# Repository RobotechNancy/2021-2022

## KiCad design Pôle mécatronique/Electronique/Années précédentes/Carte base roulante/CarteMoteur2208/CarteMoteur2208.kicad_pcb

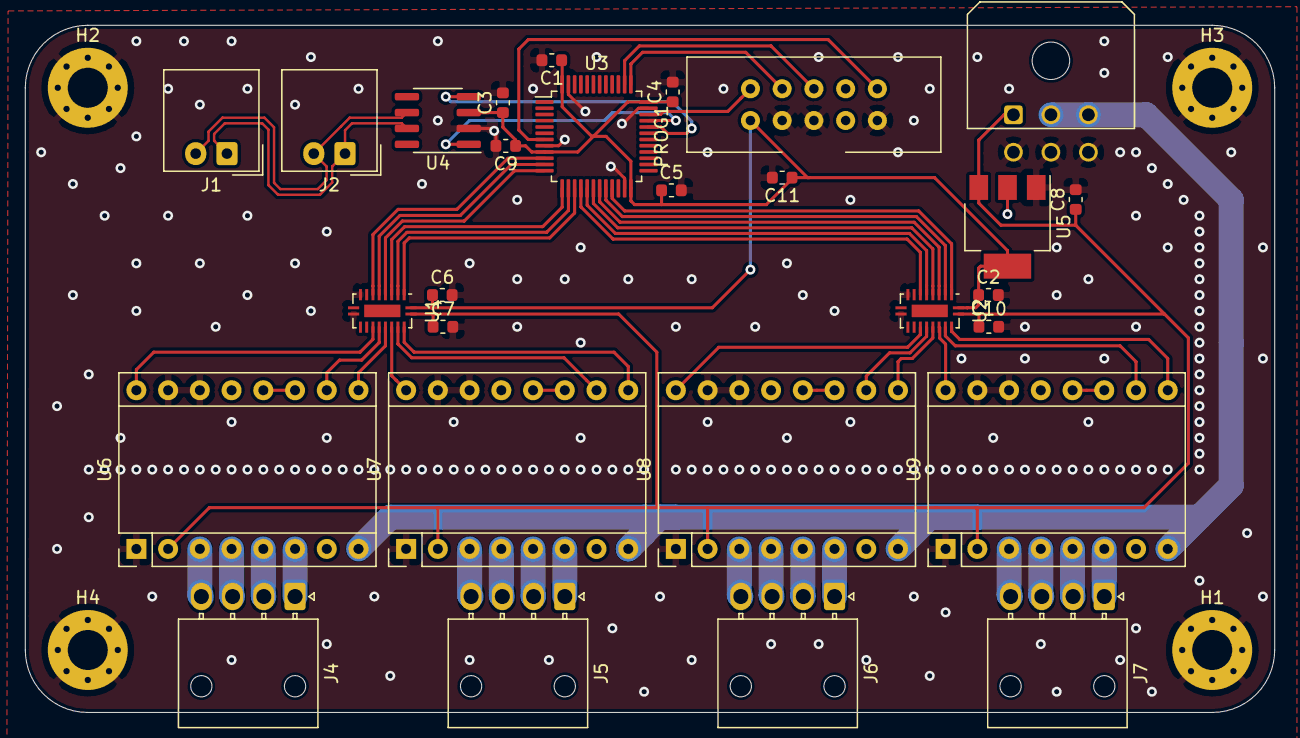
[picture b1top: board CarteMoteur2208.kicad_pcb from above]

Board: 2 copper layers, 100.0 x 55.0 mm, 32 parts (0 on the bottom side), 56 nets.

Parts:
C1, C2, C3, C4, C5, C6, C7, C8, C9, C10: 104; C_0603_1608Metric
C11: 106; C_0603_1608Metric
H1, H2, H3, H4: MountingHole_Pad; MountingHole_3.2mm_M3_Pad_Via
J1, J2: Conn_01x02; Molex_SPOX_5268-02A_1x02_P2.50mm_Horizontal
J3: Conn_02x03_Counter_Clockwise; Molex_Micro-Fit_3.0_43045-0600_2x03_P3.00mm_Horizontal
J4, J5, J6, J7: Conn_01x04; Molex_Nano-Fit_105313-xx04_1x04_P2.50mm_Horizontal
PROG1: STM32_SW; JTAG10
U1, U2: FXMA108; WQFN-20-1EP_2.5x4.5mm_P0.5mm_EP1x2.9mm
U3: STM32F103C8Tx; LQFP-48_7x7mm_P0.5mm
U4: TCAN337; SOIC-8_3.9x4.9mm_P1.27mm
U5: LT1117-3.3; SOT-223-3_TabPin2
U6, U7, U8, U9: TMC2208; Pololu_Breakout-16_15.2x20.3mm

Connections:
+3V3: C1.1, C2.1, C3.1, C4.1, C5.1, C6.1, C9.1, C11.1, PROG1.1, U1.1, U2.1, U3.9, U3.24, U3.36, U3.48, U4.3, U5.2
+5V: C7.1, C8.1, C10.1, J3.1, U1.20, U2.20, U5.3, U6.2, U7.2, U8.2, U9.2
+BATT: J3.2, J3.3, U6.8, U7.8, U8.8, U9.8
/CAN_N: J1.2, J2.2, U4.6
/CAN_P: J1.1, J2.1, U4.7
/CAN_RX: U3.32, U4.4
/CAN_TX: U3.33, U4.1
/DIR1_H: U1.16, U6.9
/DIR1_L: U1.5, U3.12
/DIR2_H: U1.19, U7.9
/DIR2_L: U1.2, U3.15
/DIR3_H: U2.16, U8.9
/DIR3_L: U2.5, U3.18
/DIR4_H: U2.19, U9.9
/DIR4_L: U2.2, U3.21
/EN1_H: U1.14, U6.16
/EN1_L: U1.7, U3.10
/EN2_H: U1.17, U7.16
/EN2_L: U1.4, U3.13
/EN3_H: U2.14, U8.16
/EN3_L: U2.7, U3.16
/EN4_H: U2.17, U9.16
/EN4_L: U2.4, U3.19
/NRST: PROG1.10, U3.7
/STEP1_H: U1.15, U6.10
/STEP1_L: U1.6, U3.11
/STEP2_H: U1.18, U7.10
/STEP2_L: U1.3, U3.14
/STEP3_H: U2.15, U8.10
/STEP3_L: U2.6, U3.17
/STEP4_H: U2.18, U9.10
/STEP4_L: U2.3, U3.20
/SWCLK: PROG1.4, U3.37
/SWDIO: PROG1.2, U3.34
/SWO: PROG1.6, U3.38
GND: C1.2, C2.2, C3.2, C4.2, C5.2, C6.2, C7.2, C8.2, C9.2, C10.2, C11.2, H1.1, H2.1, H3.1, H4.1, J3.4, J3.5, J3.6, PROG1.3, PROG1.5, PROG1.9, U1.8, U1.9, U1.10, U1.11, U2.8, U2.9, U2.10, U2.11, U3.8, U3.23, U3.35, U3.47, U4.2, U5.1, U6.1, U6.14, U6.15, U7.1, U7.14, U7.15, U8.1, U8.14, U8.15, U9.1, U9.14, U9.15
unnamed: J4.1, U6.6
unnamed: J4.2, U6.5
unnamed: J4.3, U6.4
unnamed: J4.4, U6.3
unnamed: J5.1, U7.6
unnamed: J5.2, U7.5
unnamed: J5.3, U7.4
unnamed: J5.4, U7.3
unnamed: J6.1, U8.6
unnamed: J6.2, U8.5
unnamed: J6.3, U8.4
unnamed: J6.4, U8.3
unnamed: J7.1, U9.6
unnamed: J7.2, U9.5
unnamed: J7.3, U9.4
unnamed: J7.4, U9.3
unnamed: U6.11, U6.12
unnamed: U7.11, U7.12
unnamed: U8.11, U8.12
unnamed: U9.11, U9.12

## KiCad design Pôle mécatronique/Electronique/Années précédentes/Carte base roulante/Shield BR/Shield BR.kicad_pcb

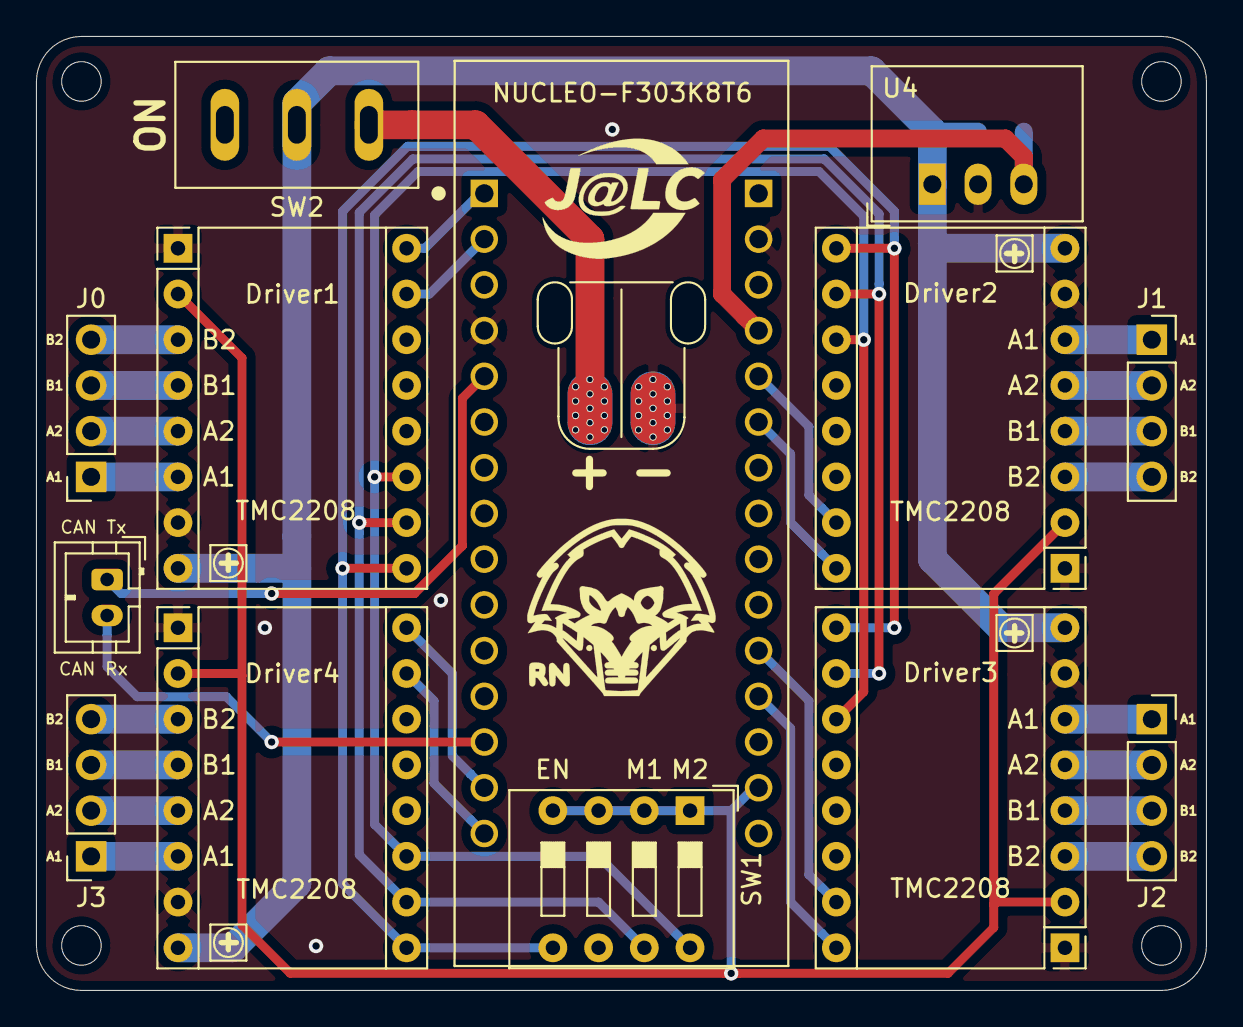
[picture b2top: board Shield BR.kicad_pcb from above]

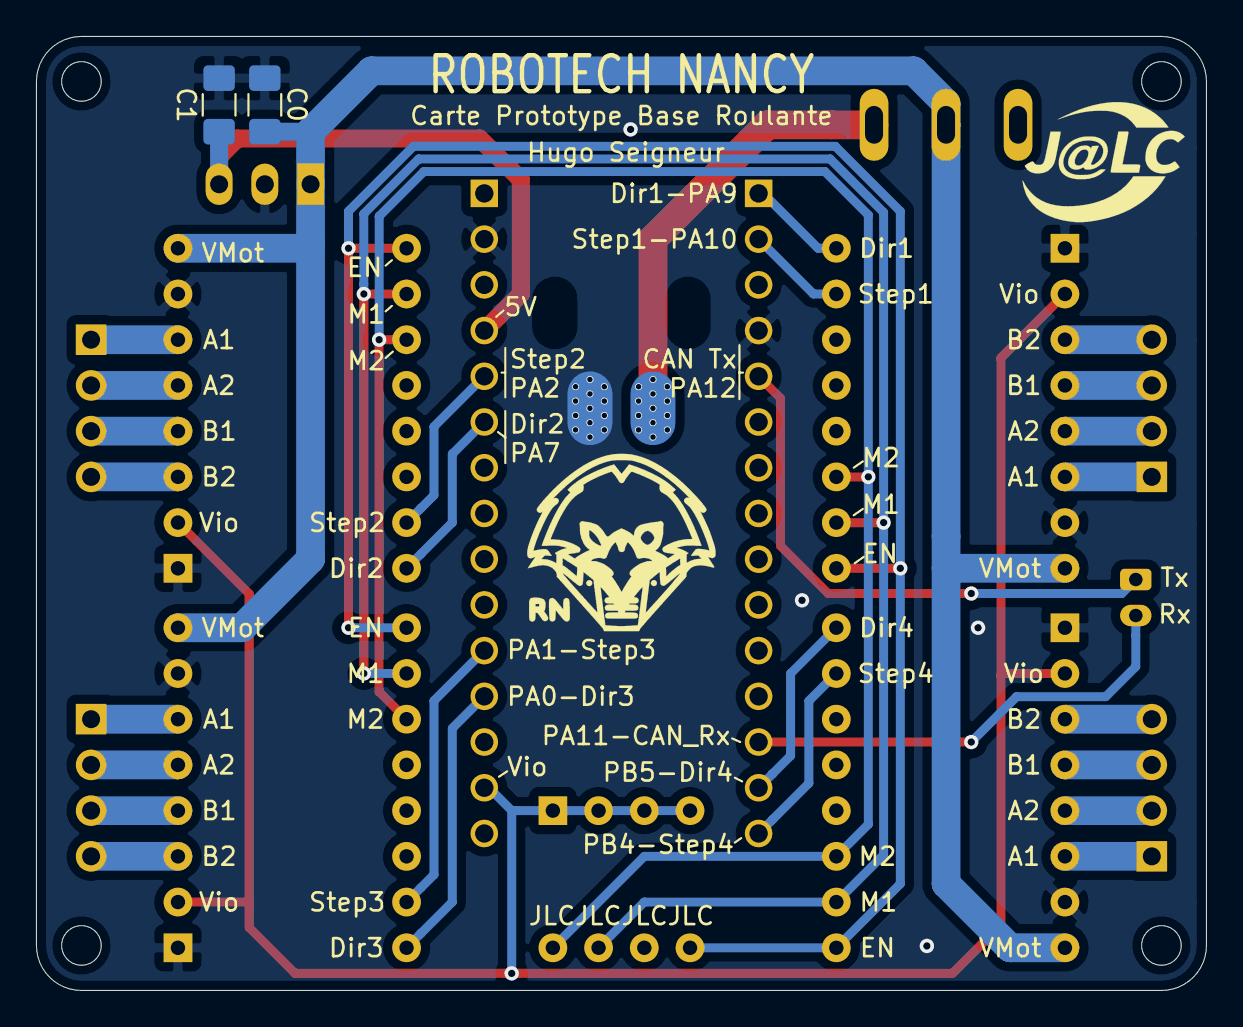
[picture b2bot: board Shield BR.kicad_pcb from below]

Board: 2 copper layers, 65.0 x 53.0 mm, 20 parts (2 on the bottom side), 34 nets.

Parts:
C0, C1: 10u; C_1206_3216Metric_Pad1.42x1.75mm_HandSolder
Driver1, Driver2, Driver3, Driver4: TMC2208; TMC_2208_BOB
H0, H1, H2, H3: MountingHole; MountingHole_2.2mm_M2_ISO7380
J0, J1, J2, J3: Conn_01x04_Female; PinSocket_1x04_P2.54mm_Vertical
J4: Conn_01x04_Male; Alim_Cablée_2_fils
J5: Conn_01x02_Female; JST_PH_B2B-PH-K_1x02_P2.00mm_Vertical
NUCLEO-F303K8T6: NUCLEO-F303K8; MODULE_NUCLEO-F303K8
SW1: SW_DIP_x04; SW_DIP_SPSTx04_Slide_9.78x12.34mm_W7.62mm_P2.54mm
SW2: SW_Push_SPDT; Switch_3_Pin
U4: R-78E5.0-0.5; Converter_DCDC_RECOM_R-78E-0.5_THT

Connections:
+5V: C1.1, NUCLEO-F303K8T6.4.4, U4.3
+BATT: C0.1, Driver1.8, Driver2.8, Driver3.8, Driver4.8, SW2.2, U4.1
CAN_Rx: J5.2, NUCLEO-F303K8T6.3.13
CAN_Tx: J5.1, NUCLEO-F303K8T6.3.5
Dir0: Driver1.9, NUCLEO-F303K8T6.3.1
Dir1: Driver2.9, NUCLEO-F303K8T6.4.6
Dir2: Driver3.9, NUCLEO-F303K8T6.4.12
Dir3: Driver4.9, NUCLEO-F303K8T6.3.14
EN: Driver1.16, Driver2.16, Driver3.16, Driver4.16, SW1.5
GND: C0.2, C1.2, Driver1.1, Driver1.7, Driver2.1, Driver2.7, Driver3.1, Driver3.7, Driver4.1, Driver4.7, J4.2, NUCLEO-F303K8T6.3.4, NUCLEO-F303K8T6.4.2, U4.2
M1: Driver1.15, Driver2.15, Driver3.15, Driver4.15, SW1.7
M2: Driver1.14, Driver2.14, Driver3.14, Driver4.14, SW1.8
unnamed: Driver1.3, J0.4
unnamed: Driver1.4, J0.3
unnamed: Driver1.5, J0.2
unnamed: Driver1.6, J0.1
unnamed: Driver2.3, J1.4
unnamed: Driver2.4, J1.3
unnamed: Driver2.5, J1.2
unnamed: Driver2.6, J1.1
unnamed: Driver3.3, J2.4
unnamed: Driver3.4, J2.3
unnamed: Driver3.5, J2.2
unnamed: Driver3.6, J2.1
unnamed: Driver4.3, J3.4
unnamed: Driver4.4, J3.3
unnamed: Driver4.5, J3.2
unnamed: Driver4.6, J3.1
unnamed: J4.1, SW2.1
Stp0: Driver1.10, NUCLEO-F303K8T6.3.2
Stp1: Driver2.10, NUCLEO-F303K8T6.4.5
Stp2: Driver3.10, NUCLEO-F303K8T6.4.11
Stp3: Driver4.10, NUCLEO-F303K8T6.3.15
Vio: Driver1.2, Driver2.2, Driver3.2, Driver4.2, NUCLEO-F303K8T6.4.14, SW1.1, SW1.2, SW1.3, SW1.4

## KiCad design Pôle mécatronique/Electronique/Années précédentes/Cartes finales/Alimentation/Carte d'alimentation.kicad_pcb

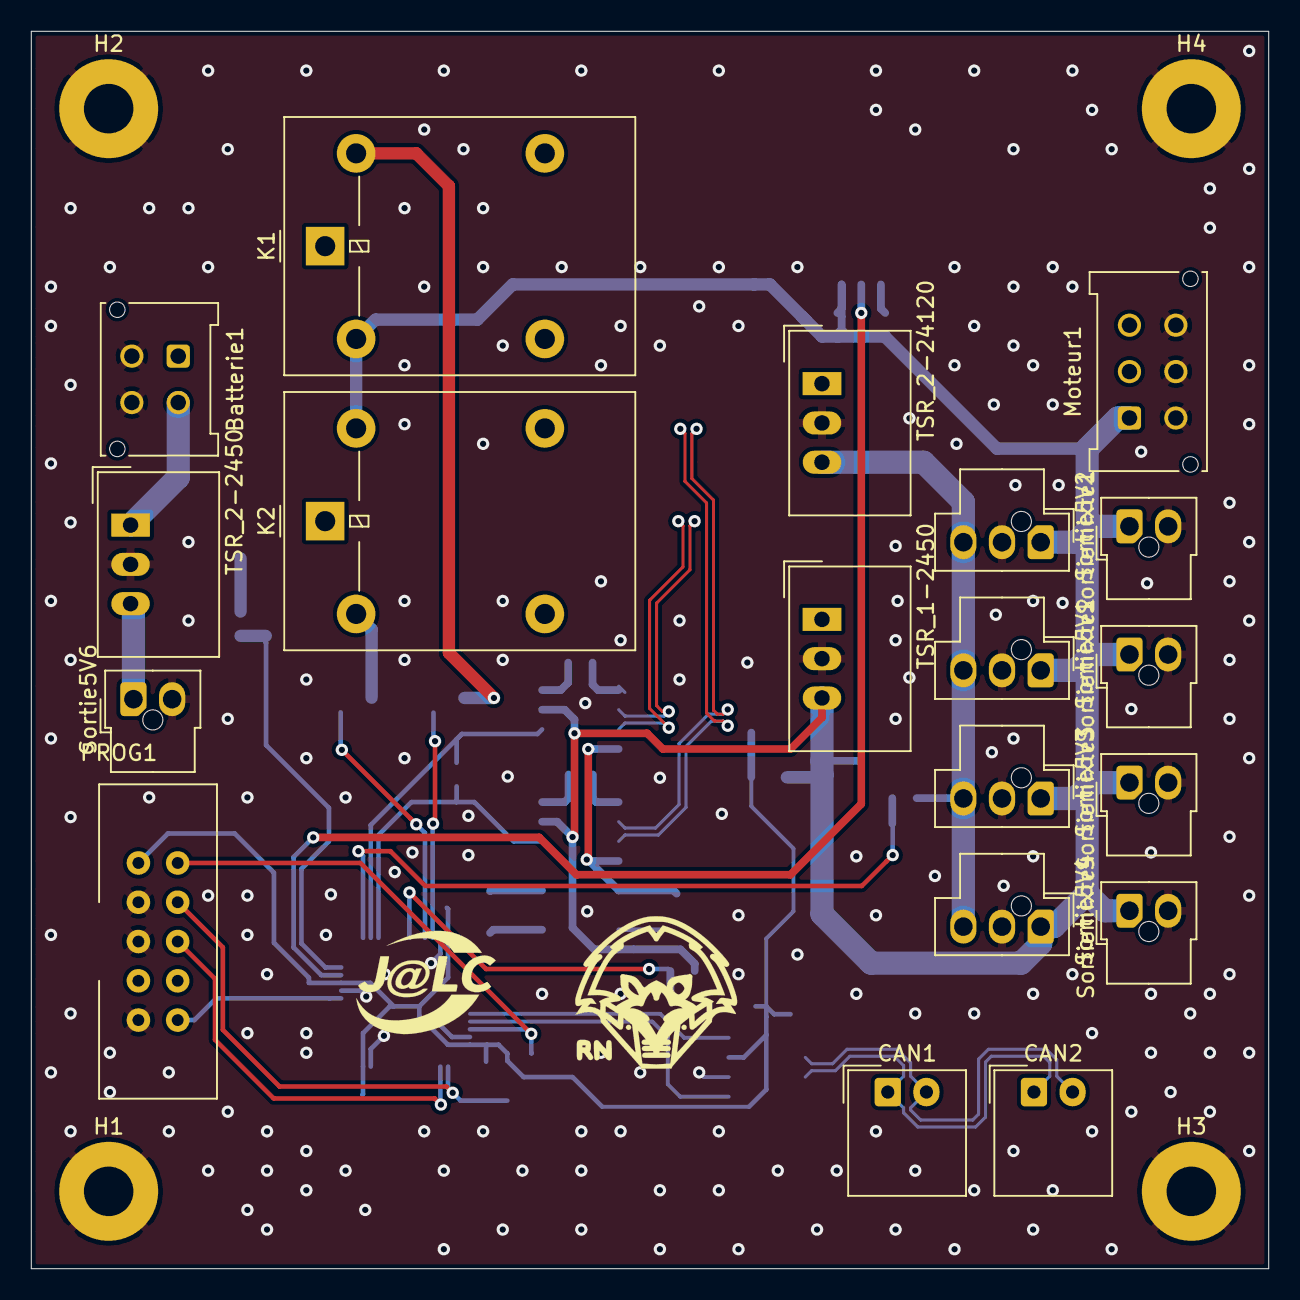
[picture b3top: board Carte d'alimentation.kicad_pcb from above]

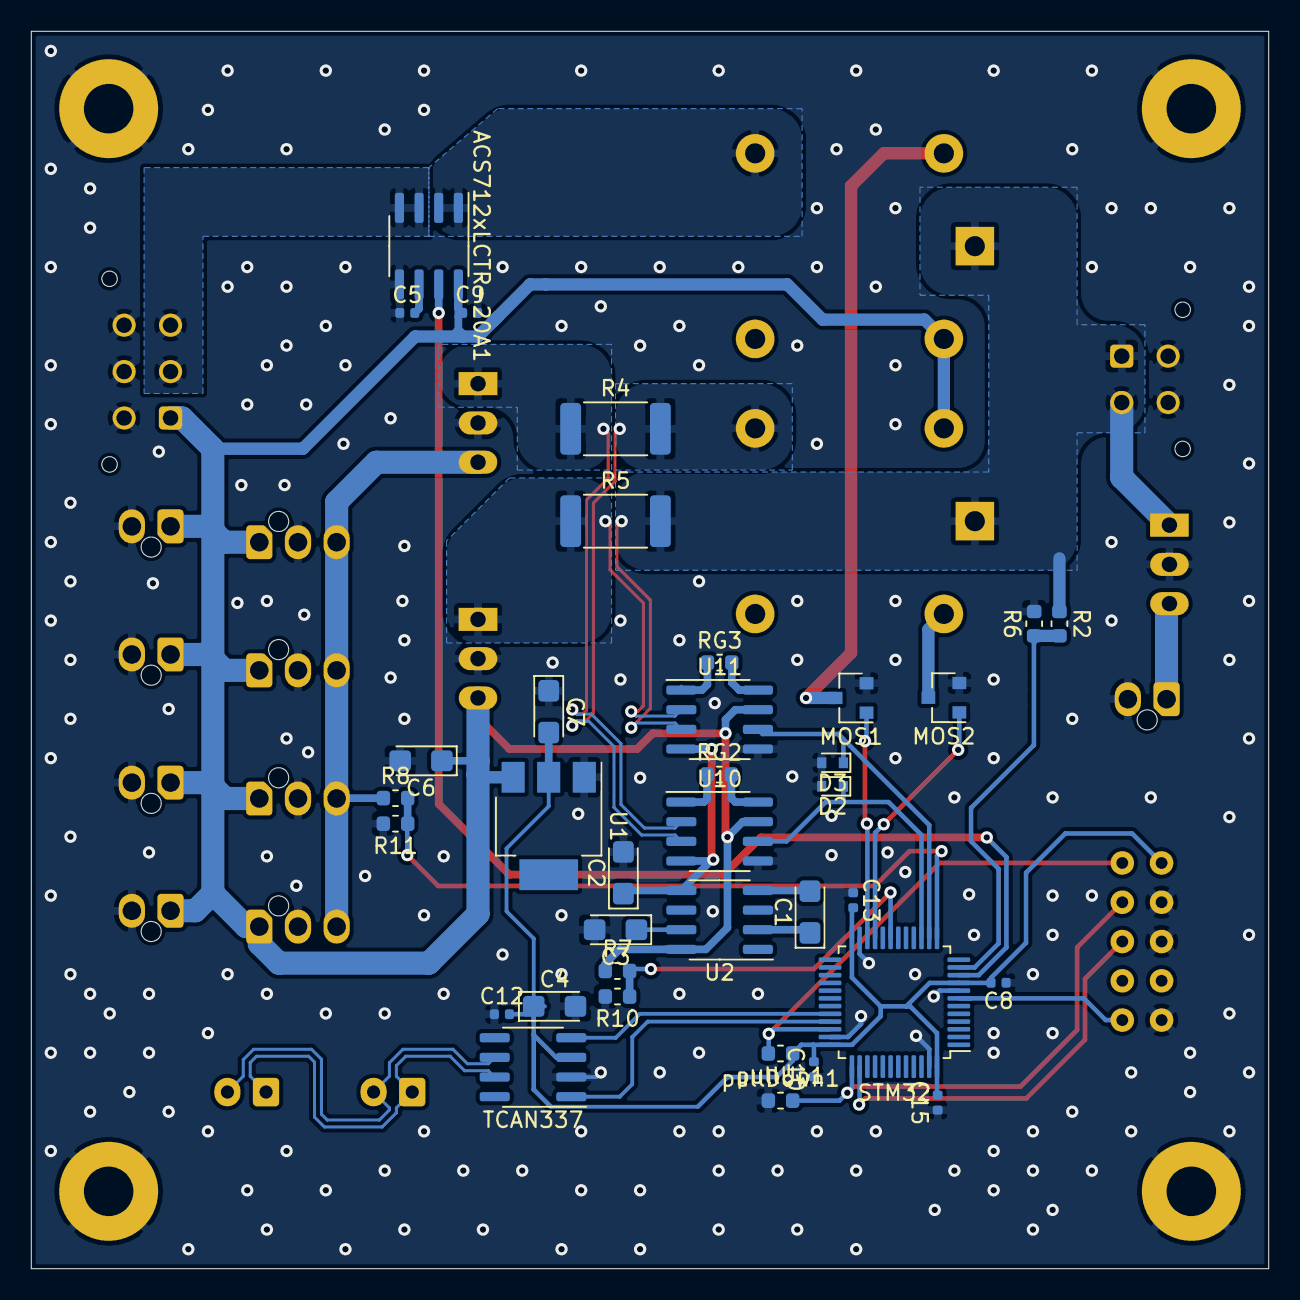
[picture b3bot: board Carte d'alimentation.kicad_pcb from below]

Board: 2 copper layers, 80.0 x 80.0 mm, 59 parts (36 on the bottom side), 38 nets.

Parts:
ACS712xLCTR-20A1: ACS712xLCTR-20A; SOIC-8_3.9x4.9mm_P1.27mm
Batterie1: Batterie; Molex_Micro-Fit_3.0_43045-0412_2x02_P3.00mm_Vertical
C1, C2, C3, C6, C7: 10µF; CP_EIA-3216-10_Kemet-I
C4: 1µF; CP_EIA-3216-10_Kemet-I
C5, C8, C9, C10, C12, C13, C15: 1nF; C_0402_1005Metric
CAN1, CAN2: sortie CAN; Molex_SPOX_5268-02A_1x02_P2.50mm_Horizontal
D2, D3: D_Zener; D_SOD-523
H1, H2, H3, H4: MountingHole_Pad; MountingHole_3.2mm_M3_Pad
K1, K2: G5LE-1; Relay_SPDT_Omron-G5LE-1
MOS1, MOS2: 2N7002; SOT-23
Moteur1: Moteur; Molex_Micro-Fit_3.0_43045-0612_2x03_P3.00mm_Vertical
PROG1: STM32_SW; JTAG10
R2: 90k; R_0603_1608Metric
R4, R5: 0.035; R_2512_6332Metric
R6, R7: 10k; R_0603_1608Metric
R8: 56k; R_0603_1608Metric
R10, R11: 20k; R_0603_1608Metric
RG2: 1150; R_0603_1608Metric
RG3: 560; R_0603_1608Metric
STM32: STM32F103C8Tx; LQFP-48_7x7mm_P0.5mm
Sortie5V1, Sortie5V2, Sortie5V3, Sortie5V4, Sortie5V6: Sortie 5V; Molex_Nano-Fit_105309-xx02_1x02_P2.50mm_Vertical
Sortiemixte1, Sortiemixte2, Sortiemixte3, Sortiemixte4: Sortie mixte; Molex_Nano-Fit_105309-xx03_1x03_P2.50mm_Vertical
TCAN337: TCAN337; SOIC-8_3.9x4.9mm_P1.27mm
TSR_1-2450: TSR_1-2450; Converter_DCDC_TRACO_TSR-1_THT
TSR_2-2450: TSR_2-2450; Converter_DCDC_TRACO_TSR-1_THT
TSR_2-24120: TSR_2-24120; Converter_DCDC_TRACO_TSR-1_THT
U1: LM1117-3.3; SOT-223
U2: ICL7660; SOIC-8_3.9x4.9mm_P1.27mm
U10, U11: AD620; SOIC-8_3.9x4.9mm_P1.27mm
pullDown1: 1k; R_0603_1608Metric
pullUp1: 1k; R_0603_1608Metric

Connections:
3.3V: C4.1, C7.2, C8.2, C10.2, C12.2, C13.2, C15.2, PROG1.1, STM32.9, STM32.24, STM32.36, STM32.48, TCAN337.3, U1.2, pullUp1.1
5VDCRasPi: Sortie5V6.1, TSR_2-2450.3
+5V: ACS712xLCTR-20A1.8, C6.1, C9.1, K1.2, K2.5, Moteur1.1, R7.1, Sortie5V1.1, Sortie5V2.1, Sortie5V3.1, Sortie5V4.1, Sortiemixte1.1, Sortiemixte2.1, Sortiemixte3.1, Sortiemixte4.1, TSR_1-2450.3, U1.3, U2.8, U10.7, U11.7
+12V: R8.1, Sortiemixte1.3, Sortiemixte2.3, Sortiemixte3.3, Sortiemixte4.3, TSR_2-24120.3
-5V: C2.1, U2.5, U10.4, U11.4
/AD5_N: R5.1, TSR_1-2450.1, U11.2
/AD12_N: R4.1, TSR_2-24120.1, U10.2
/AD12_P: K2.4, R4.2, U10.3
GND: ACS712xLCTR-20A1.5, Batterie1.3, Batterie1.4, C2.2, C3.2, C4.2, C5.1, C6.2, C7.1, C8.1, C9.2, C10.1, C12.1, C13.1, C15.1, D2.2, D3.2, H1.1, H2.1, H3.1, H4.1, MOS1.2, MOS2.2, Moteur1.4, Moteur1.5, Moteur1.6, PROG1.3, PROG1.5, PROG1.9, R6.2, R10.2, R11.2, STM32.8, STM32.23, STM32.35, STM32.47, Sortie5V1.2, Sortie5V2.2, Sortie5V3.2, Sortie5V4.2, Sortie5V6.2, Sortiemixte1.2, Sortiemixte2.2, Sortiemixte3.2, Sortiemixte4.2, TCAN337.2, TSR_1-2450.2, TSR_2-2450.2, TSR_2-24120.2, U1.1, U2.3, U10.5, U11.5, pullDown1.1
I_5VDC: D3.1, STM32.14, U11.6
I_12VDC: D2.1, STM32.15, U10.6
I_VBatt: ACS712xLCTR-20A1.7, STM32.10
Mes_5VDC: R7.2, R10.1, STM32.19
Mes_12VDC: R8.2, R11.1, STM32.13
Mes_VBatt: R2.2, R6.1, STM32.11
NRST: PROG1.10, STM32.7
unnamed: ACS712xLCTR-20A1.1, ACS712xLCTR-20A1.2, K1.4
unnamed: ACS712xLCTR-20A1.6, C5.2
unnamed: C1.1, U2.2
unnamed: C1.2, U2.4
unnamed: C3.1, U2.7
unnamed: K1.5, MOS1.3
unnamed: K2.2, MOS2.3
unnamed: RG2.1, U10.1
unnamed: RG2.2, U10.8
unnamed: RG3.1, U11.1
unnamed: RG3.2, U11.8
Out_VBatt: ACS712xLCTR-20A1.3, ACS712xLCTR-20A1.4, Moteur1.2, Moteur1.3
Relay_12V: MOS2.1, STM32.21
Relay_VBatt: MOS1.1, STM32.22
Rx: STM32.32, TCAN337.4
SWCLK: PROG1.4, STM32.37, pullDown1.2
SWDIO: PROG1.2, STM32.34, pullUp1.2
SWO: PROG1.6, STM32.38
Tx: STM32.33, TCAN337.1
VBatt: Batterie1.1, Batterie1.2, K1.1, K2.1, R2.1, R5.2, TSR_2-2450.1, U11.3
can_N: CAN1.2, CAN2.2, TCAN337.6
can_P: CAN1.1, CAN2.1, TCAN337.7

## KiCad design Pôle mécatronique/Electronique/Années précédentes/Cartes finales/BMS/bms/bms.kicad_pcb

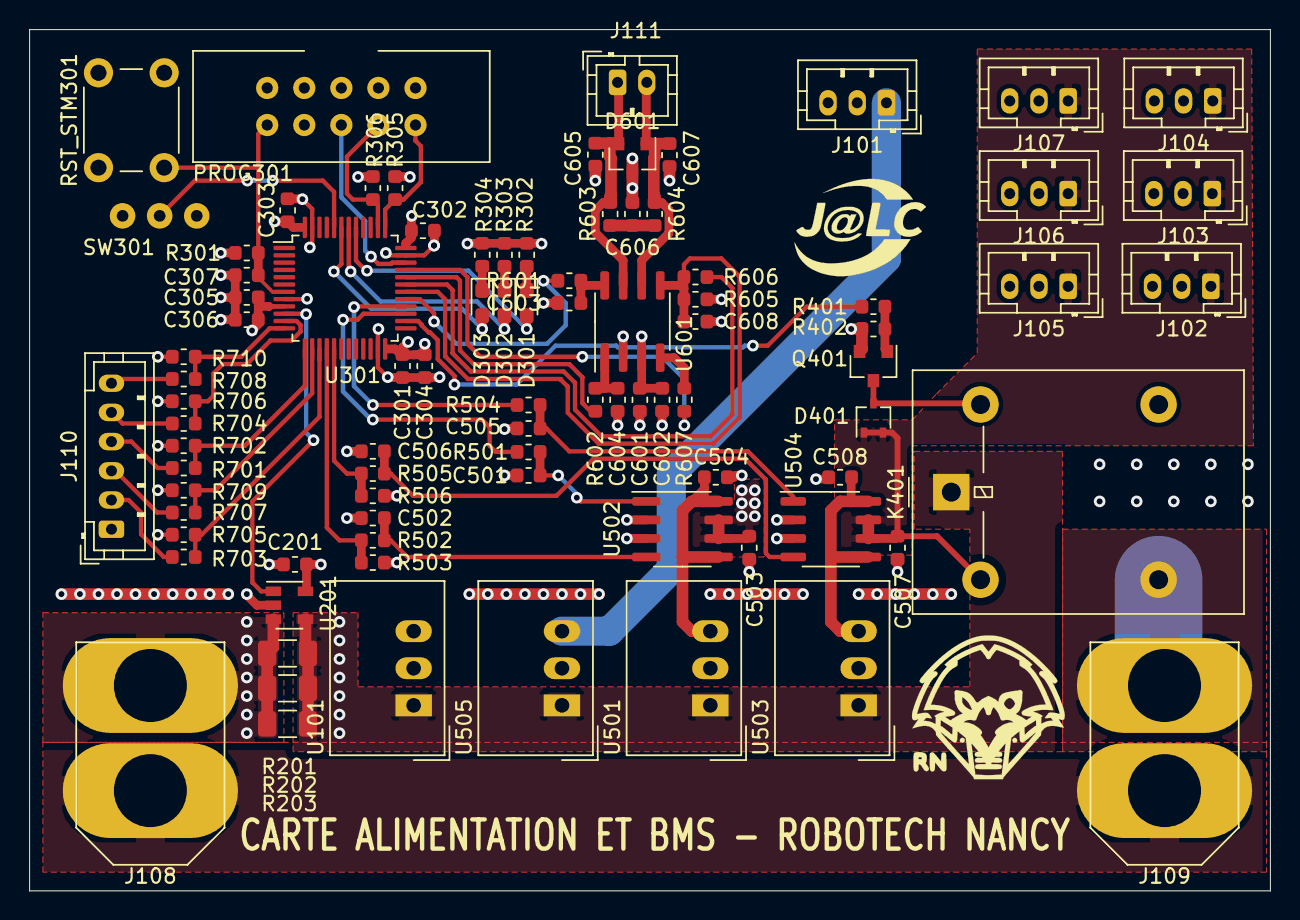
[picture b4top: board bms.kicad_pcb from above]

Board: 4 copper layers, 85.0 x 59.0 mm, 88 parts (0 on the bottom side), 54 nets.

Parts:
C201, C301, C302, C303, C307, C501, C504, C505, C508, C601: 100n; C_0603_1608Metric
C304, C602: 10u; C_0603_1608Metric
C305, C502, C503, C506, C507, C603, C604, C605, C606, C607, C608: 10n; C_0603_1608Metric
C306: 1u; C_0603_1608Metric
D301, D302, D303: LED; LED_0603_1608Metric_Pad1.05x0.95mm_HandSolder
D401: BAT54CW; SOT-323_SC-70
D601: D_Zener_x2_ACom_KKA; SOT-23
J101, J102, J103, J104, J105, J106, J107: Conn_01x03; JST_PH_B3B-PH-K_1x03_P2.00mm_Vertical
J108, J109: XT60
J110: Conn_01x06; JST_PH_B6B-PH-K_1x06_P2.00mm_Vertical
J111: Conn_01x02 JST; JST_PH_B2B-PH-K_1x02_P2.00mm_Vertical
K401: G5LE-1; Relay_SPDT_Omron-G5LE-1
PROG301: JTAG; JTAG10
Q401: BSS138; SOT-23
R201, R202, R203: 22m; R_1206_3216Metric
R301, R305, R306, R402, R501, R502, R503, R504, R505, R506, R605, R702, R705, R706, R709, R710: 10k; R_0603_1608Metric
R302, R303, R304: 220; R_0603_1608Metric
R401, R601: 1k; R_0603_1608Metric
R602, R606, R607: 0R; R_0603_1608Metric
R603, R604: 56; R_0603_1608Metric
R701: 33k; R_0603_1608Metric
R703: 4.7k; R_0603_1608Metric
R704: 47k; R_0603_1608Metric
R707: 18k; R_0603_1608Metric
R708: 68k; R_0603_1608Metric
RST_STM301: BTN 6x6; SW_PUSH_6mm
SW301: SW_SPDT; SW_2P2T_2.54_01x03
U101: TSR_1-2433; Converter_DCDC_TRACO_TSR-1_THT
U201: ZXCT1084E5TA; SOT-23-5
U301: STM32; LQFP-48_7x7mm_P0.5mm
U501: TSR_1-24120; Converter_DCDC_TRACO_TSR-1_THT
U502: NCV84140DR2G; SOIC-8_3.9x4.9mm_P1.27mm
U503, U505: TSR_1-2450; Converter_DCDC_TRACO_TSR-1_THT
U504: NCV84140DR2G; SO-8_3.9x4.9mm_P1.27mm
U601: TCAN337; SOIC-8_3.9x4.9mm_P1.27mm

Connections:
+3V3: C201.1, C301.1, C302.1, C303.1, C304.1, C305.1, C306.1, C601.1, C602.1, PROG301.1, R301.1, R305.1, R605.1, SW301.1, U101.3, U201.5, U301.9, U301.24, U301.36, U301.48, U502.2, U504.2, U601.3
+5P: J101.1, U505.3
+5V: C507.1, D401.1, D401.2, J102.1, J103.1, J104.1, J105.1, J106.1, J107.1, K401.2, U504.6, U504.7
+12V: C503.1, J102.3, J103.3, J104.3, J105.3, J106.3, J107.3, U502.6, U502.7
/Adaptation/OUT1: R703.2, R705.1, U301.15
/Adaptation/OUT2: R707.2, R709.1, U301.14
/Adaptation/OUT3: R701.2, R702.1, U301.13
/Adaptation/OUT4: R704.2, R706.1, U301.11
/Adaptation/OUT5: R708.2, R710.1, U301.12
/CAN_FAULT: C608.1, R605.2, R606.2, U301.30, U601.5
/CAN_N: C607.2, D601.1, J111.2, R604.2, U601.6
/CAN_P: C605.1, D601.2, J111.1, R603.1, U601.7
/CAN_RX: R607.1, U301.33
/CAN_SHDN: R606.1, U301.31
/CAN_SILENT: R601.2, U301.29
/CAN_TX: R602.2, U301.32
/CELL1: J110.2, R703.1
/CELL2: J110.3, R707.1
/CELL3: J110.4, R701.1
/CELL4: J110.5, R704.1
/CELL5: J110.6, R708.1
/EN_5V: R504.2, U301.28
/EN_12V: R501.2, U301.27
/EN_XT60: R401.2, U301.26
/IN_XT60: J108.2, R201.2, R202.2, R203.2, U201.3
/I_5V: R505.1, R506.2, U301.17
/I_12V: R502.1, R503.2, U301.16
/I_GENERAL: U201.1, U301.10
/Microcontrolleur/BOOT: SW301.2, U301.44
/Microcontrolleur/LED1: D301.2, U301.41
/Microcontrolleur/LED2: D302.2, U301.42
/Microcontrolleur/LED3: D303.2, U301.43
/Microcontrolleur/SWCLK: PROG301.4, R306.1, U301.38
/Microcontrolleur/SWDIO: PROG301.2, R305.2, U301.37
/Microcontrolleur/SWO: PROG301.6, U301.34
/Microcontrolleur/nRST: C307.1, PROG301.10, R301.2, RST_STM301.2, U301.7
/OUT_XT60: J109.2, K401.3
/Régulateur/CS_5V: C506.1, R505.2, U504.4
/Régulateur/CS_12V: C502.1, R502.2, U502.4
/Régulateur/OUT_EN_5V: C505.1, R504.1, U504.1
/Régulateur/OUT_EN_12V: C501.1, R501.1, U502.1
/Régulateur/OUT_REGUL_5V: C508.1, U503.3, U504.5, U504.8
/Régulateur/OUT_REGUL_12V: C504.1, U501.3, U502.5, U502.8
/TCAN/CAN_RX_DIRECT: R607.2, U601.4
/TCAN/CAN_SILENT_FILTERED: C603.1, R601.1, U601.8
/TCAN/CAN_TX_FILTERED: C604.1, R602.1, U601.1
/UNREGULATED_POWER: K401.1, R201.1, R202.1, R203.1, U101.1, U201.4, U501.1, U503.1, U505.1
GND: C201.2, C301.2, C302.2, C303.2, C304.2, C305.2, C306.2, C307.2, C501.2, C502.2, C503.2, C504.2, C505.2, C506.2, C507.2, C508.2, C601.2, C602.2, C603.2, C604.2, C605.2, C606.2, C607.1, C608.2, D601.3, J101.2, J102.2, J103.2, J104.2, J105.2, J106.2, J107.2, J108.1, J109.1, J110.1, PROG301.3, PROG301.5, PROG301.9, Q401.2, R302.1, R303.1, R304.1, R306.2, R402.1, R503.1, R506.1, R702.2, R705.2, R706.2, R709.2, R710.2, RST_STM301.1, SW301.3, U101.2, U201.2, U301.8, U301.23, U301.35, U301.47, U501.2, U502.3, U503.2, U504.3, U505.2, U601.2
unnamed: C606.1, R603.2, R604.1
unnamed: D301.1, R302.2
unnamed: D302.1, R303.2
unnamed: D303.1, R304.2
unnamed: D401.3, K401.5, Q401.3
unnamed: Q401.1, R401.1, R402.2

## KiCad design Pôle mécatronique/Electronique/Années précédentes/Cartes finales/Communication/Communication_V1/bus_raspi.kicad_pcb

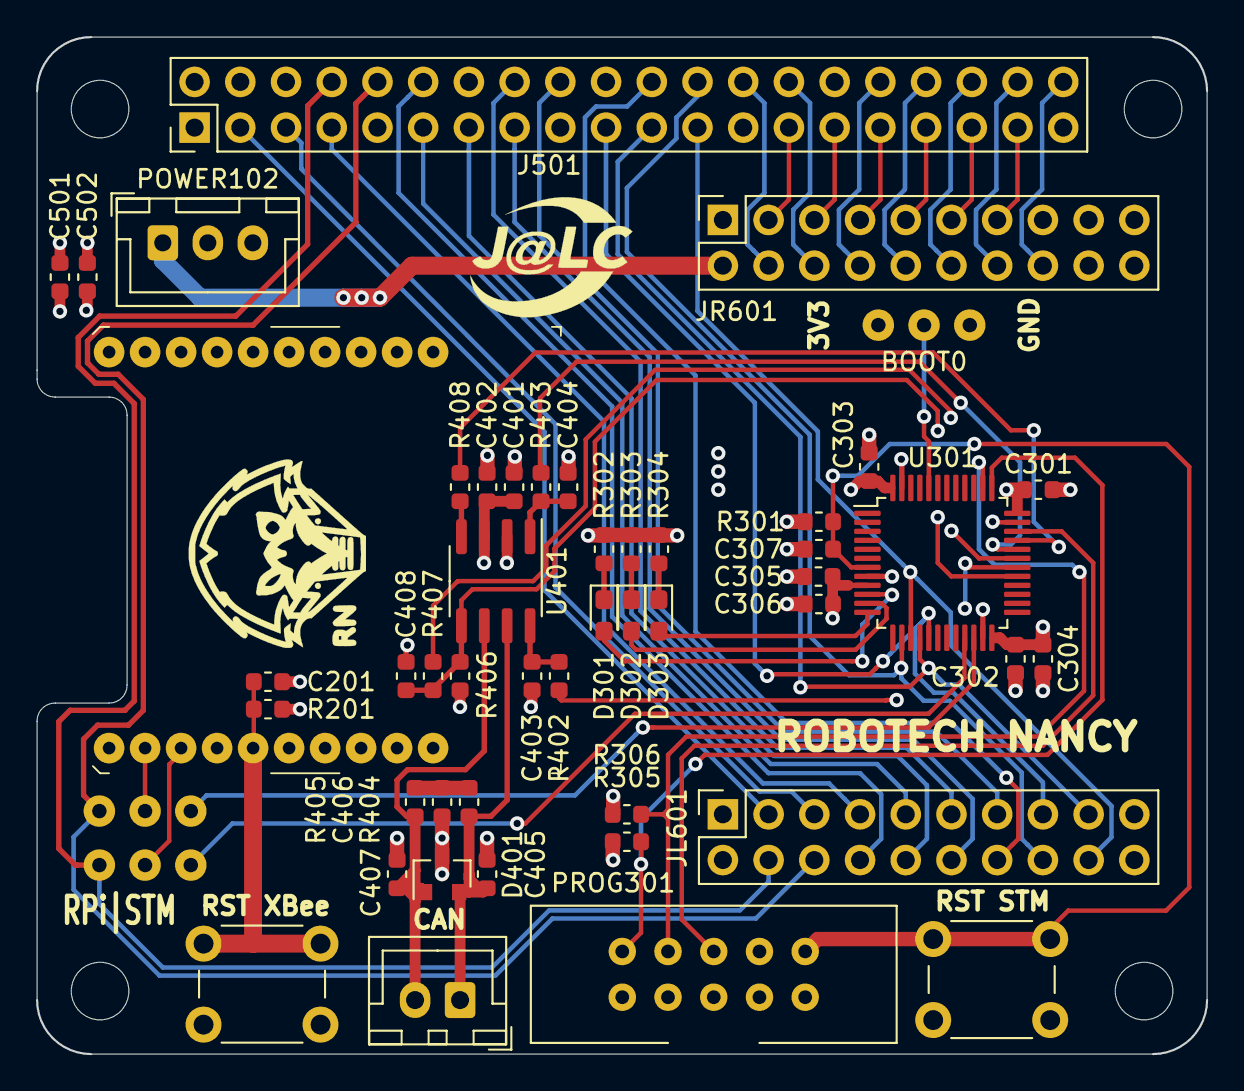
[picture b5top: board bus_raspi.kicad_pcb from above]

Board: 4 copper layers, 65.0 x 56.5 mm, 50 parts (0 on the bottom side), 59 nets.

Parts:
BOOT0: SW_SPDT; SW_2P2T_2.54_01x03
C201, C301, C302, C303, C307, C401, C501: 100n; C_0603_1608Metric
C304, C402, C502: 10u; C_0603_1608Metric
C305, C403, C404, C405, C406, C407, C408: 10n; C_0603_1608Metric
C306: 1u; C_0603_1608Metric
D301, D302, D303: LED; LED_0603_1608Metric_Pad1.05x0.95mm_HandSolder
D401: D_Zener_x2_ACom_KKA; SOT-23
J401: Conn_01x02 JST; JST_XH_B2B-XH-A_1x02_P2.50mm_Vertical
J501: Conn_02x20 PS; PinHeader_2x20_P2.54mm_Vertical
JL601: Conn_02x10 PS; PinSocket_2x10_P2.54mm_Vertical
JR601: Conn_02x10 PS; PinSocket_2x10_P2.54mm_Vertical
POWER102: Conn_01x03 JST; JST_XH_B3B-XH-A_1x03_P2.50mm_Vertical
PROG301: JTAG; JTAG10
R201, R301, R305, R306, R406: 10k; R_0603_1608Metric
R302, R303, R304: 220; R_0603_1608Metric
R402: 1k; R_0603_1608Metric
R403, R407, R408: 0R; R_0603_1608Metric
R404, R405: 56; R_0603_1608Metric
RST_STM301: BTN 6x6; SW_PUSH_6mm
RST_XB201: BTN 6x6; SW_PUSH_6mm
SW201, SW202: SW 2P2T; SW_2P2T_2.54_01x03
U201: XBee; XBEE_PRO-20_THT
U301: STM32; LQFP-48_7x7mm_P0.5mm
U401: TCAN337; SOIC-8_3.9x4.9mm_P1.27mm

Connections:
+3V3: BOOT0.1, C301.1, C302.1, C303.1, C304.1, C305.1, C306.1, C401.1, C402.1, J501.1, J501.17, JL601.1, JR601.1, PROG301.1, R201.1, R301.1, R305.1, R406.1, U201.1, U301.9, U301.24, U301.36, U301.48, U401.3
+5V: C501.1, C502.1, J501.2, J501.4, JL601.2, JR601.2, POWER102.1
/STM32/BOOT: BOOT0.2, U301.44
/STM32/LED1: D301.2, U301.10
/STM32/LED2: D302.2, U301.11
/STM32/LED3: D303.2, U301.12
/STM32/SWCLK: PROG301.4, R306.1, U301.38
/STM32/SWDIO: PROG301.2, R305.2, U301.37
/STM32/SWO: PROG301.6, U301.34
/STM32/nRST: C307.1, PROG301.10, R301.2, RST_STM301.2, U301.7
/TCAN/CAN_N: C407.2, D401.1, J401.2, R405.2, U401.6
/TCAN/CAN_P: C405.1, D401.2, J401.1, R404.1, U401.7
/TCAN/CAN_RX_DIRECT: R408.2, U401.4
/TCAN/CAN_SILENT_FILTERED: C403.1, R402.1, U401.8
/TCAN/CAN_TX_FILTERED: C404.1, R403.1, U401.1
/XBee/XBEE_RST: C201.1, R201.2, RST_XB201.2, U201.5
CAN_FAULT: C408.1, R406.2, R407.2, U301.29, U401.5
CAN_SHDN: R407.1, U301.31
CAN_SILENT: R402.2, U301.30
CE0: J501.24, JL601.16, U301.14
GND: BOOT0.3, C201.2, C301.2, C302.2, C303.2, C304.2, C305.2, C306.2, C307.2, C401.2, C402.2, C403.2, C404.2, C405.2, C406.2, C407.1, C408.2, C501.2, C502.2, D401.3, J501.6, J501.9, J501.14, J501.20, J501.25, J501.30, J501.39, JL601.19, JL601.20, JR601.15, JR601.17, JR601.18, JR601.19, JR601.20, POWER102.2, PROG301.3, PROG301.5, PROG301.9, R302.1, R303.1, R304.1, R306.2, RST_STM301.1, RST_XB201.1, U201.10, U301.8, U301.23, U301.35, U301.47, U401.2
MISO: J501.21, JL601.17, U301.16
MOSI: J501.19, JL601.15, U301.17
unnamed: C406.1, R404.2, R405.1
unnamed: D301.1, R302.2
unnamed: D302.1, R303.2
unnamed: D303.1, R304.2
P3: J501.3, JL601.3
P5: J501.5, JL601.5
P7: J501.7, JL601.7
P8: J501.8, JL601.4, SW202.1
P10: J501.10, JL601.6, SW201.1
P11: J501.11, JL601.9
P12: J501.12, JL601.8
P13: J501.13, JL601.10
P15: J501.15, JL601.12
P16: J501.16, JL601.11
P18: J501.18, JL601.13
P22: J501.22, JL601.14
P23: J501.23, JL601.18, U301.15
P26: J501.26, JR601.4
P27: J501.27, JR601.3
P28: J501.28, JR601.6
P29: J501.29, JR601.5
P31: J501.31, JR601.7
P32: J501.32, JR601.8
P33: J501.33, JR601.9
P34: J501.34, JR601.10
P35: J501.35, JR601.11
P36: J501.36, JR601.12
P37: J501.37, JR601.13
P38: J501.38, JR601.14
P40: J501.40, JR601.16
RXD_TCAN337: R408.1, U301.33
TXD_TCAN337: R403.2, U301.32
UART_RX_STM: SW201.3, U301.22
UART_RX_Xbee: SW202.2, U201.3
UART_TX_STM: SW202.3, U301.21
UART_TX_Xbee: SW201.2, U201.2

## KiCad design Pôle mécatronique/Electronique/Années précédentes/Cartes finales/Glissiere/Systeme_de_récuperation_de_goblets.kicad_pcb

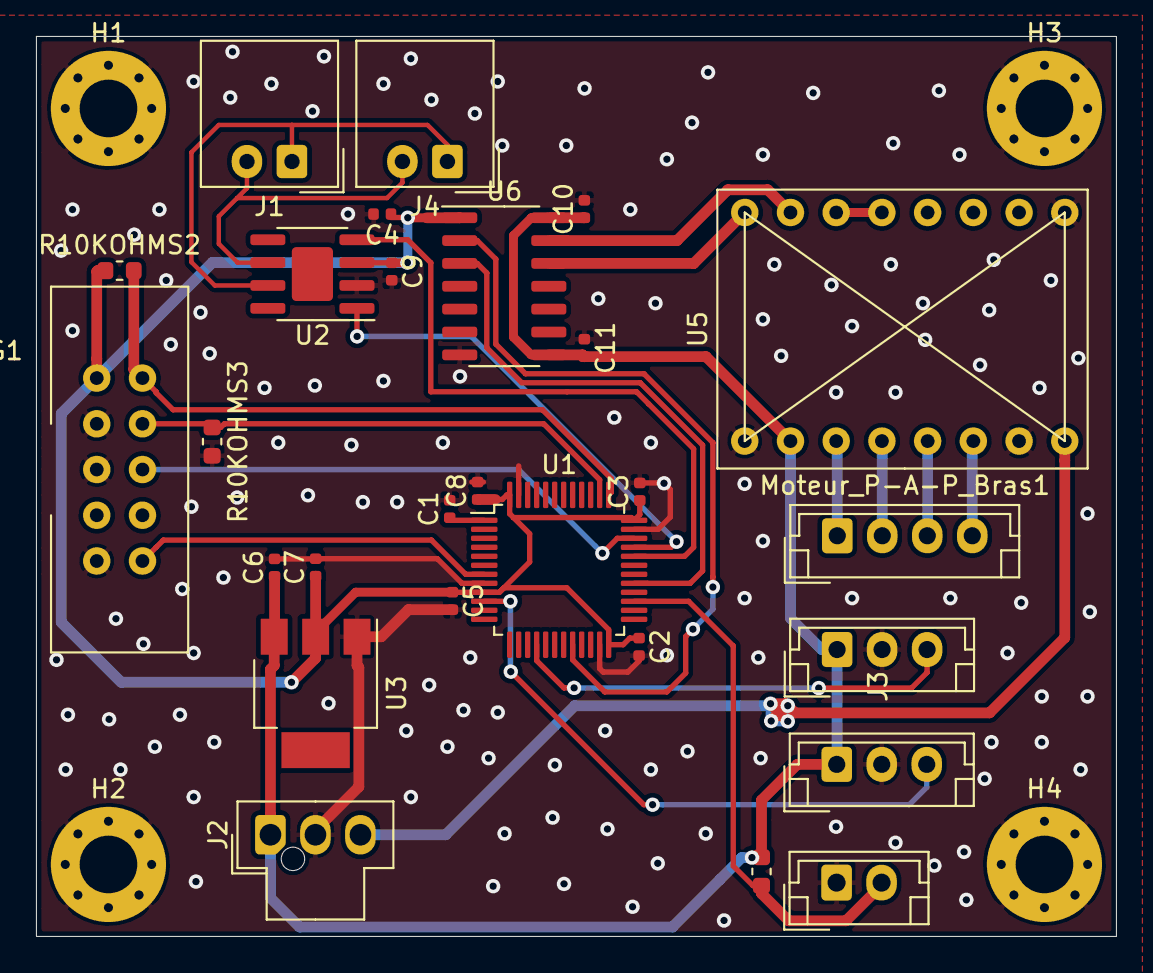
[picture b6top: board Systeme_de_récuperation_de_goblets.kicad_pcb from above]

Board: 2 copper layers, 60.0 x 50.0 mm, 31 parts (0 on the bottom side), 25 nets.

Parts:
C1, C2, C3, C4, C5, C8, C9, C10, C11: 10 nF; C_0402_1005Metric
C6, C7: 22µF; C_0402_1005Metric
H1, H2, H3, H4: MountingHole_Pad; MountingHole_3.2mm_M3_Pad_Via
J1, J4: Bus_CAN; Molex_SPOX_5268-02A_1x02_P2.50mm_Horizontal
J2: Conn_Alim; Molex_Nano-Fit_105309-xx03_1x03_P2.50mm_Vertical
J3: Conn_01x02_Female; JST_EH_B2B-EH-A_1x02_P2.50mm_Vertical
Moteur_P-A-P_Bras1: Conn_01x04_Female; JST_EH_B4B-EH-A_1x04_P2.50mm_Vertical
PROG1: STM32_SW; JTAG10
R10KOHMS1, R10KOHMS2, R10KOHMS3: R_Small; R_0603_1608Metric
Servo_Bras_Pince1: Conn_01x03_Female; JST_EH_B3B-EH-A_1x03_P2.50mm_Vertical
Servo_Bras_Poignet1: Conn_01x03_Female; JST_EH_B3B-EH-A_1x03_P2.50mm_Vertical
U1: STM32F103C8Tx; LQFP-48_7x7mm_P0.5mm
U2: TCAN337; SOIC-8-1EP_3.9x4.9mm_P1.27mm_EP2.29x3mm
U3: AMS1117-3.3; SOT-223
U5: TMC2208
U6: TXB0104D; SOIC-14_3.9x8.7mm_P1.27mm

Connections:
+3V3: C2.1, C3.1, C4.1, C5.1, C7.1, C8.1, C9.1, PROG1.1, R10KOHMS2.1, U1.9, U1.24, U1.36, U1.48, U2.3, U3.2, U6.1
+5V: C6.1, C10.1, C11.2, J2.1, R10KOHMS1.2, Servo_Bras_Pince1.1, Servo_Bras_Poignet1.1, U3.3, U5.2, U6.8, U6.14
+12V: J2.3, U5.8
CAN_H: J1.1, J4.1, U2.7
CAN_L: J1.2, J4.2, U2.6
CAN_RX: U1.32, U2.4
CAN_TX: U1.33, U2.1
CLK: U5.11, U5.12
DIR_Moteur_P-A-P_Bras: U1.20, U6.2
Fin_De_Course_Bras: J3.2, R10KOHMS1.1, U1.27
GND: C1.2, C2.2, C3.2, C4.2, C5.2, C6.2, C7.2, C8.2, C9.2, C10.2, C11.1, H1.1, H2.1, H3.1, H4.1, J2.2, J3.1, PROG1.3, PROG1.5, PROG1.9, R10KOHMS3.2, Servo_Bras_Pince1.2, Servo_Bras_Poignet1.2, U1.8, U1.23, U1.35, U1.47, U2.2, U3.1, U5.1, U5.7, U5.16, U6.7
H2: U5.9, U6.13
H6: U5.10, U6.12
M1A_Bras: Moteur_P-A-P_Bras1.3, U5.5
M1B_Bras: Moteur_P-A-P_Bras1.4, U5.6
M2A_Bras: Moteur_P-A-P_Bras1.2, U5.4
M2B_Bras: Moteur_P-A-P_Bras1.1, U5.3
NRST: PROG1.10, U1.7
unnamed: C1.1, U1.1
PWM_Pince_Bras: Servo_Bras_Pince1.3, U1.10
PWM_Poignet_Bras: Servo_Bras_Poignet1.3, U1.16
STEP_Moteur_P-A-P_Bras: U1.29, U6.3
SWCLK: PROG1.4, R10KOHMS3.1, U1.38
SWDIO: PROG1.2, R10KOHMS2.2, U1.37
SWO: PROG1.6, U1.34
